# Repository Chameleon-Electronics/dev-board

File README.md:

<!--
Add one of this in front of the title

-->

# Dev Board 

<!--
Describe briefly but descritively the device
-->
The board we use to prototype our ideas, this is where it all starts.

## Features

- Breadboard friendly
- USB connection
- SWD Debug adapter

<!--
Features that anyone would understand
Don't mention components or types of components (relays, transistors, etc)
A good example: Makes sandiwiches for free!
A bad example: SSR for quiet/durable operation
-->

<!--
Separatly mention architectural features, be as technical as you can but briefly
mention SSRs, operating frequency, etc
-->

<!--- DON'T CHANGE BELLOW THIS LINE -->

## Not working? Have an improvement idea?
Open an issue or if you're feeling excited submit a pull request! We are always looking for new features and improvements.

## License
You can use this at your will provided that you mention us properly by including a link to this page.

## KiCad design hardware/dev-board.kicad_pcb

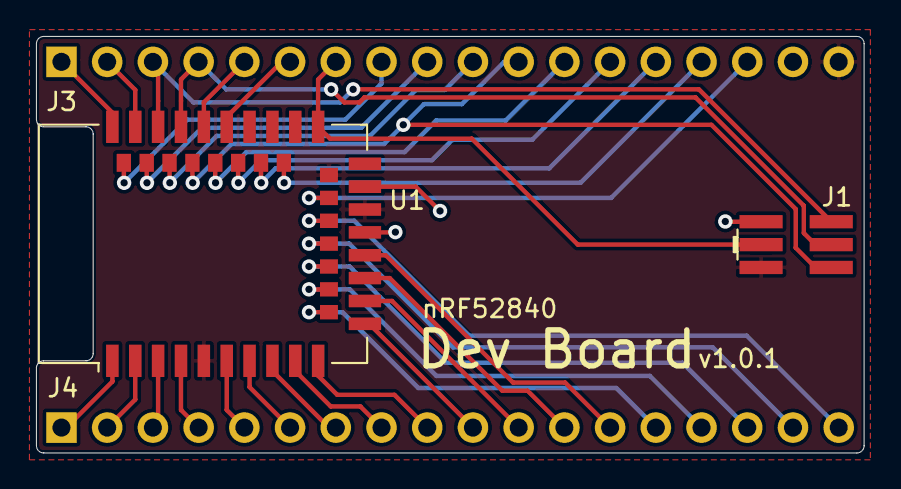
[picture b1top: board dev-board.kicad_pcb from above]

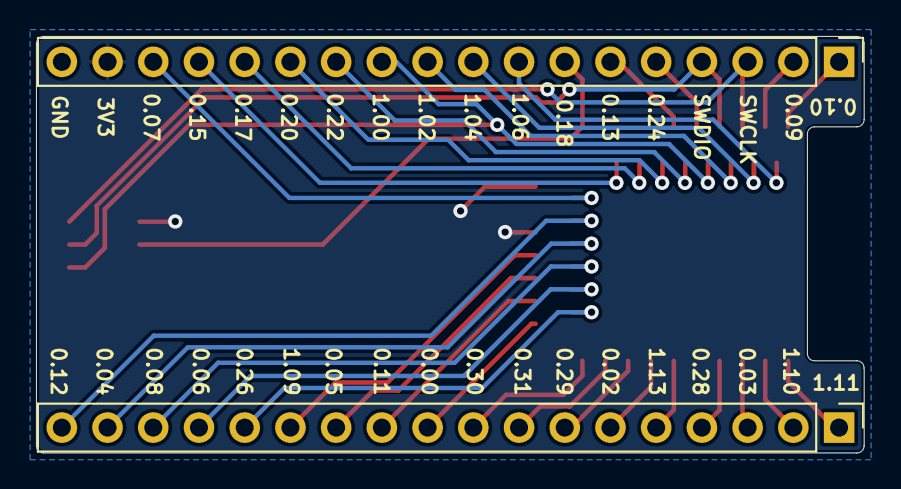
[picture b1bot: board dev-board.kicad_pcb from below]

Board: 2 copper layers, 46.0 x 23.1 mm, 4 parts (2 on the bottom side), 36 nets.

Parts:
J1: Conn_Chameleon_SWD; Chameleon_SWD_Header
J3, J4: Conn_01x18_Male; PinHeader_1x18_P2.54mm_Vertical
U1: E73-2G4M08S1C

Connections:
+3V3: J1.1, J3.17, U1.19, U1.23
/P0.00: J4.10, U1.11
/P0.02: J4.6, U1.7
/P0.03: J4.3, U1.3
/P0.04: J4.17, U1.18
/P0.05: J4.12, U1.15
/P0.06: J4.15, U1.14
/P0.07: J3.16, U1.22
/P0.08: J4.16, U1.16
/P0.09: J3.2, U1.41
/P0.10: J3.1, U1.43
/P0.11: J4.11, U1.13
/P0.12: J4.18, U1.20
/P0.13: J3.6, U1.33
/P0.15: J3.15, U1.28
/P0.17: J3.14, U1.30
/P0.18: J1.3, J3.7, U1.26
/P0.20: J3.13, U1.32
/P0.22: J3.12, U1.34
/P0.24: J3.5, U1.35
/P0.26: J4.14, U1.12
/P0.28: J4.4, U1.4
/P0.29: J4.7, U1.8
/P0.30: J4.9, U1.10
/P0.31: J4.8, U1.9
/P1.02: J3.10, U1.38
/P1.04: J3.9, U1.40
/P1.06: J3.8, U1.42
/P1.09: J4.13, U1.17
/P1.10: J4.2, U1.2
/P1.11: J4.1, U1.1
/P1.13: J4.5, U1.6
/SWDCLK: J1.2, J3.3, U1.39
/SWDIO: J1.4, J3.4, U1.37
/SWO: J1.6, J3.11, U1.36
GND: J1.5, J3.18, U1.5, U1.21, U1.24

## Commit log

2020-06-02 Add KiCAD Library
2020-06-02 USB Type C
2020-06-02 Dev Board v1.0.0.0
2020-06-02 Update PCB render
2020-06-02 Updated Description
2020-06-02 Antenna keepout zone and rounded PCB corners
2020-06-10 Use standard Debug connector (#2) and USB impendance matched (#3)
2020-06-17 Release 1.0.0
2020-07-01 nrf52820 schematic
2020-09-18 Fix Silkcreen Pin
2020-09-18 Update render and silkcreen version number
